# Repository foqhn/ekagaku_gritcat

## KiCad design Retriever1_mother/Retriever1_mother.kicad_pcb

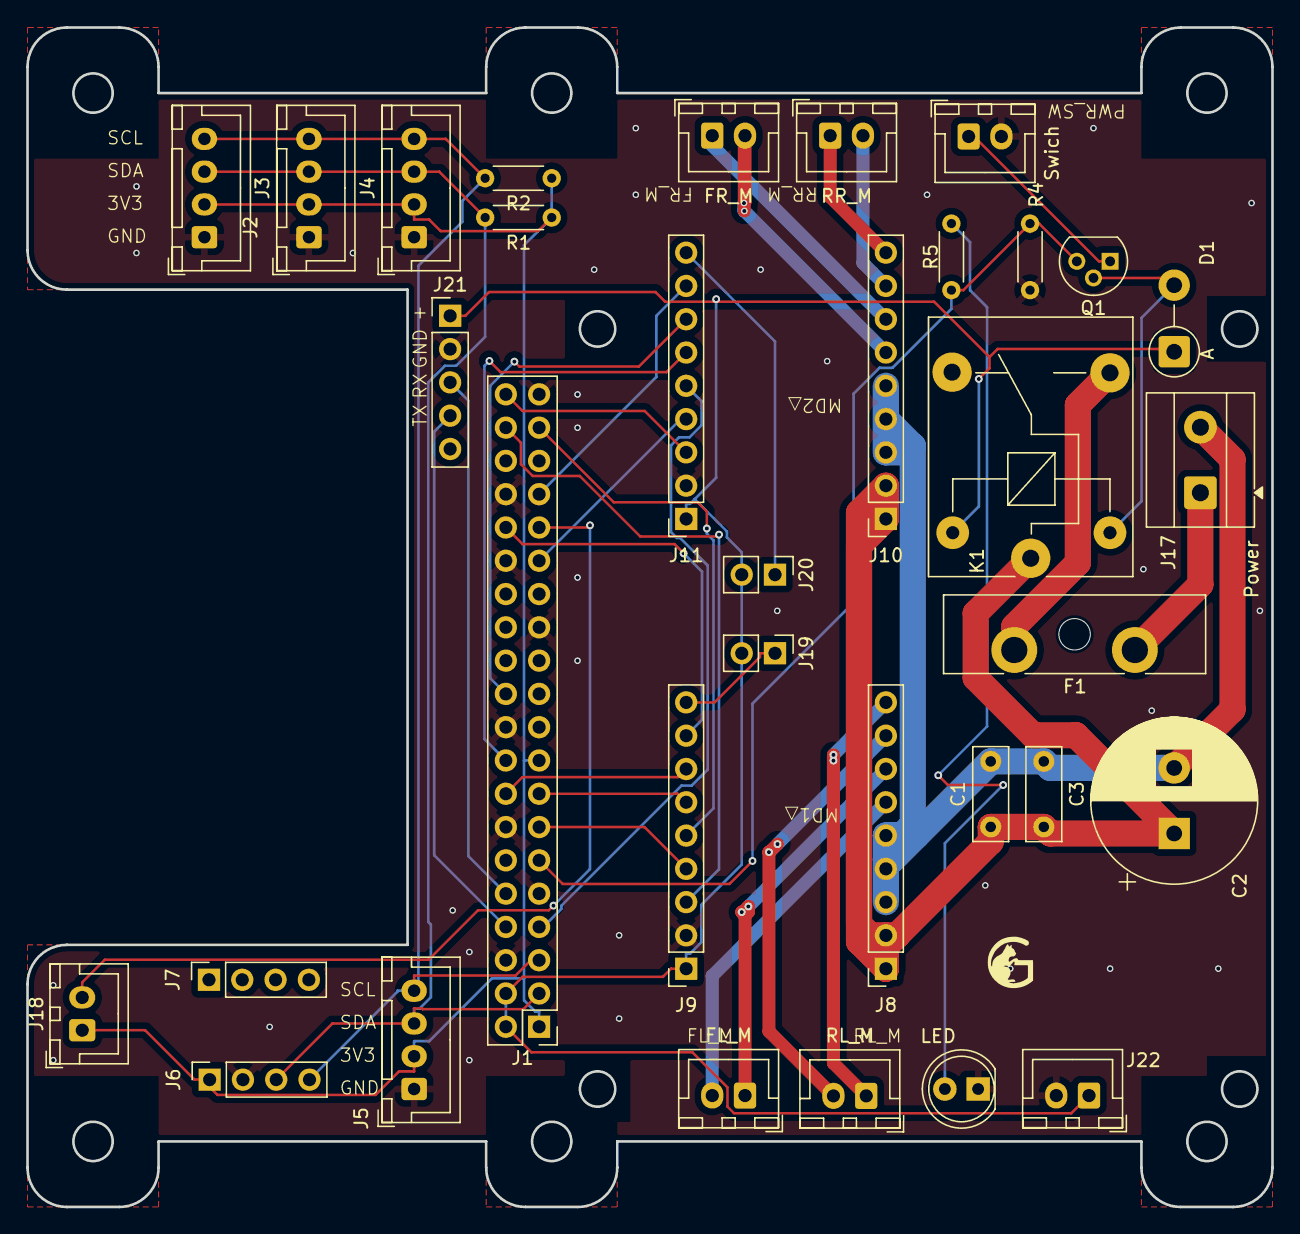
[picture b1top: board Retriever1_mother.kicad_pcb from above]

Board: 2 copper layers, 95.0 x 90.0 mm, 34 parts (0 on the bottom side), 38 nets.

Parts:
C1, C3: C; C_Disc_D7.0mm_W2.5mm_P5.00mm
C2: 100uF; CP_Radial_D12.5mm_P5.00mm
D1: D; D_DO-15_P5.08mm_Vertical_AnodeUp
D2: LED; LED_D5.0mm
F1: Fuse; Fuseholder_Blade_ATO_Littelfuse_Pudenz_2_Pin
J1: Raspberry_Pi_4; PinHeader_2x20_P2.54mm_Vertical
J2, J3, J4, J5: Conn_01x04_Pin; JST_XH_B4B-XH-A_1x04_P2.50mm_Vertical
J6, J7: Conn_01x04_Pin; PinSocket_1x04_P2.54mm_Vertical
J8, J9, J10, J11: Conn_01x09_Pin; PinSocket_1x09_P2.54mm_Vertical
J12: FL_M; JST_XH_B2B-XH-A_1x02_P2.50mm_Vertical
J13: FR_M; JST_XH_B2B-XH-A_1x02_P2.50mm_Vertical
J14: RL_M; JST_XH_B2B-XH-A_1x02_P2.50mm_Vertical
J15: RR_M; JST_XH_B2B-XH-A_1x02_P2.50mm_Vertical
J16: Swich; JST_XH_B2B-XH-A_1x02_P2.50mm_Vertical
J17: Power; TerminalBlock_MetzConnect_Type055_RT01502HDWU_1x02_P5.00mm_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
J18, J22: Conn_01x02_Pin; JST_XH_B2B-XH-A_1x02_P2.50mm_Vertical
J19, J20: Conn_01x02_Pin; PinHeader_1x02_P2.54mm_Vertical
J21: Conn_01x05_Pin; PinHeader_1x05_P2.54mm_Vertical
K1: SANYOU_SRD_Form_C; Relay_SPDT_SANYOU_SRD_Series_Form_C
Q1: NPN; TO-92
R1, R2: 10k; R_Axial_DIN0204_L3.6mm_D1.6mm_P5.08mm_Horizontal
R4: 470; R_Axial_DIN0204_L3.6mm_D1.6mm_P5.08mm_Horizontal
R5: 200; R_Axial_DIN0204_L3.6mm_D1.6mm_P5.08mm_Horizontal

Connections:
+3.3V: J1.1 (3V3), J1.17 (3V3), J2.2, J3.2, J4.2, J5.2, J6.1, J18.1, R1.1, R2.1
+5V: D1.1 (K), J1.2 (5V), J1.4 (5V), J9.1, J11.1, J19.2, J20.2, J21.1, J22.1, K1.5
+12V: F1.1, J17.1
/TB6612基盤1/AO_1: J10.6, J13.2
/TB6612基盤1/AO_2: J10.7, J13.1
/TB6612基盤1/BO_1: J10.8, J15.2
/TB6612基盤1/BO_2: J10.9, J15.1
/TB6612基盤1/STBY: J11.9, J20.1
/TB6612基盤/AO_1: J8.6, J12.2
/TB6612基盤/AO_2: J8.7, J12.1
/TB6612基盤/BO_1: J8.8, J14.2
/TB6612基盤/BO_2: J8.9, J14.1
/TB6612基盤/STBY: J9.9, J19.1
/TB6612基盤/VM: C1.1, C2.1, C3.1, J8.1, J8.2, J10.1, J10.2, K1.1
Ext_Sw: J1.31 (GPCLK2/GPIO06), J18.2
FL_1: J1.15 (GPIO22/SDIO_CLK), J9.6
FL_2: J1.16 (GPIO23/SDIO_CMD), J9.7
FL_PWM: J1.32 (GPIO12/PWM0), J9.8
FR_1: J1.18 (GPIO24/SDIO_DAT0), J11.6
FR_2: J1.22 (GPIO25/SDIO_DAT1), J11.7
FR_PWM: J1.33 (GPIO13/PWM1), J11.8
GND: D2.1 (K), J1.6 (GND), J1.9 (GND), J1.14 (GND), J1.20 (GND), J1.25 (GND), J1.30 (GND), J1.34 (GND), J1.39 (GND), J2.1, J3.1, J4.1, J5.1, J6.2, J9.2, J11.2, J16.2, J21.2, J22.2, R4.1
GNDPWR: C1.2, C2.2, C3.2, J8.3, J8.4, J8.5, J10.3, J10.4, J10.5, J17.2
unnamed: D1.2 (A), K1.2, Q1.3 (C)
unnamed: D2.2 (A), R5.2
unnamed: F1.2, K1.3
unnamed: J16.1, Q1.2 (E)
RL_1: J1.37 (GPIO26/SDIO_DAT2), J9.5
RL_2: J1.13 (GPIO27/SDIO_DAT3), J9.4
RL_PWM: J1.38 (GPIO20/SPI1_MOSI/PCM_DIN/PWM1), J9.3
RR_1: J1.7 (GPCLK0/GPIO04), J11.5
RR_2: J1.29 (GPCLK1/GPIO05), J11.4
RR_PWM: J1.40 (GPIO21/SPI1_SCLK/PCM_DOUT), J11.3
SCL: J1.5 (SCL_I2C1/GPIO03), J2.4, J3.4, J4.4, J5.4, J6.4, R2.2
SDA: J1.3 (SDA_I2C1/GPIO02), J2.3, J3.3, J4.3, J5.3, J6.3, R1.2
SD_Swich: J1.11 (GPIO17/SPI1_~CE1), Q1.1 (B), R4.2, R5.1
UART1_RX: J1.10 (GPIO15/UART_RXD), J21.3
UART1_TX: J1.8 (GPIO14/UART_TXD), J21.4

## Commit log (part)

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2025-10-16 first
2025-10-17 md update
2025-10-19 app update
2025-10-19 gpt update
2025-10-19 back
2025-10-19 shutdown update
2025-10-19 checkpoint1019
2025-10-20 server and fe
2025-10-20 ws ui update
2025-10-20 ui server update
2025-10-29 fe update
2025-11-06 index update
2025-11-06 wifi update
2025-11-06 nodejs
2025-11-07 jsx updtae
2025-11-07 jsx up
2025-11-07 sensor node auto run
2025-11-08 gps update
2025-11-08 css update
2025-11-09 1741
2025-11-09 description added
2025-11-09 Fix formatting in setup instructionsa
2025-11-09 Improve formatting of setup instructions
    Updated item list formatting with line breaks for clarity.
2025-11-23 circuit
2025-12-07 blockly
2025-12-07 gitignore
2025-12-07 program_run
2025-12-08 disc
2025-12-08 Refactor Raspberry Pi setup instructionsa
    Removed unnecessary line breaks in setup instructions for rosdep and bno055 package.
2025-12-09 images
2025-12-09 Fix image paths in Raspberry Pi setup document
2025-12-09 Fix image paths in Raspberry Pi setup document
    Updated image paths in the Raspberry Pi setup instructions to ensure correct display.
2025-12-09 Fix typo in Raspberry Pi setup instructions
2025-12-09 Update Raspberry Pi setup instructions formatting
    Replace line breaks with HTML <br> tags for formatting.
2025-12-09 Fix formatting and add line breaks in setup guide
2025-12-09 Fix formatting and update service setup instructions
2025-12-09 Rename setup guide to assembly instructions
2025-12-09 Add line break tag in Raspberry Pi setup instructions
    Updated instructions to include HTML line break tag for clarity.
2025-12-15 UI update
2025-12-19 Fix chmod command for network config file
2025-12-24 latest
2026-02-26 Add WiFi setup instructions to Raspberry Pi guide
    Added instructions for adding or changing WiFi settings.
2026-03-28 260329
2026-03-28 chash deleted
2026-04-15 webRTC
2026-04-17 aaaa0417
2026-04-17 だけど，
2026-04-19 latest0419
2026-04-19 Update service dependencies in Raspberry Pi setup
    Change service startup dependencies from network-online to network.
2026-04-21 Fix typo in requirements file name
2026-04-21 turn
2026-04-21 stun added
2026-04-21 stun modified
2026-04-21 message added
2026-04-22 offer modified
2026-04-24 server update
2026-04-24 base
2026-05-06 oled
2026-05-06 time
2026-05-06 while
2026-05-06 done?
2026-05-19 log system update
2026-05-19 GPS 403 update
2026-05-19 ignore
2026-05-19 reflesh button added
